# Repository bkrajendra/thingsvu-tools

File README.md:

<h1 align="center">thingsvu-tools</h1>

<p align="center">
  <b>AI-assisted design tools for embedded products — schematic, PCB, and enclosure — built on KiCad.</b>
</p>

<p align="center">

</p>

---

## What is thingsvu-tools?

thingsvu-tools lets an AI assistant work alongside you in KiCad. You describe the circuit you want; the assistant plans the change, shows you exactly what it will do, and — once you approve — builds it in your schematic. Every result is checked against KiCad itself before it is reported back to you.

It connects to any assistant that speaks the [Model Context Protocol](https://modelcontextprotocol.io) (MCP), such as Claude Desktop, Claude Code, or VS Code.

> [!NOTE]
> **Third-party tools.** Whole-board autorouting (`pcb_autoroute_plan`) is done by [Freerouting](https://github.com/freerouting/freerouting), a separate open-source project (GPL-3.0) by its own authors; thingsvu-tools is not affiliated with it. It is optional: it is only used after you set it up (see [Optional: the autorouter](#optional-the-autorouter)), runs on your machine with its network features turned off, and its results are checked by KiCad's own DRC before they are kept. Everything else, including explicit routing, pours, and placement, is done by thingsvu-tools and KiCad itself.

## Why it's different

- **You stay in control.** Changes are proposed as a plan first. Nothing touches your design until you confirm it, and a stale plan is never applied to a document that has changed.
- **Verified, not assumed.** After every change, the tools read the design back from KiCad — symbols, values, and net connections — and run ERC. A check that couldn't run is reported as such, never as a pass.
- **Readable schematics.** Generated schematics read like a person drew them: signal flows left to right, power and ground are symbols, parts are wired, not just labelled.
- **Describe intent, not coordinates.** Say "R1 pin 2 and R2 pin 1 share net MID"; the tools take care of placement, wiring, and labels on the proper grid.
- **Built on KiCad's official API.** First-class support for KiCad 11's schematic API, with a fallback that works on KiCad 10 through the schematic file. You always know which features your KiCad version supports.
- **Works live, headless, or on a file.** Co-edit in the open Schematic Editor with normal undo, generate and verify designs without a GUI, or edit a schematic file with no KiCad running at all.
- **Local and private.** Everything runs on your machine. No cloud service, no open network ports, and your design files stay where they are.
- **Fast and dependable.** Written in Rust as a small set of native binaries — no Python runtime to manage.

## Quick start (Windows)

You need **KiCad 11** (or the 10.99 nightly) for live editing, or **KiCad 10** for the file mode, and an AI assistant that supports MCP. No administrator rights are needed: everything is installed under your user profile.

### 1. Install

**Option A — download.** Get `thingsvu-tools-v<version>-windows-x64.zip` from the [latest release](https://github.com/bkrajendra/thingsvu-tools/releases/latest), extract it, and run `install.ps1` (right-click → **Run with PowerShell**).

**Option B — one line.** In PowerShell:

```powershell
irm https://raw.githubusercontent.com/bkrajendra/thingsvu-tools/main/scripts/install.ps1 | iex
```

This downloads the newest release, checks it against its published checksum, and installs it. Read the [script](scripts/install.ps1) first if you like; it is short.

The installer:

1. puts `kicad-ai-mcp.exe` in `%LOCALAPPDATA%\thingsvu\kicad-ai\bin`;
2. installs the **KiCad AI** plugin into your KiCad 11 plugin folder (`Documents\KiCad\<version>\plugins`) — KiCad 10 cannot run schematic plugins, so it is skipped there;
3. offers to add the server to **Claude Code** and **Claude Desktop** (it keeps a backup of any settings file it changes);
4. tells you what to do next.

Useful options: `-Yes` (answer yes to everything), `-NoPlugin`, `-SkipClients`, `-KicadVersion 11.0`, `-Version 0.1.0`.

### 2. Turn on KiCad's API (KiCad 11, live editing)

In KiCad: **Preferences → Plugins**, enable the **KiCad API**, then restart KiCad. If you only use the file mode, skip this.

### 3. Connect your assistant

The installer does this for Claude Code and Claude Desktop. For anything else, the server is a program that speaks MCP over stdio:

<details>
<summary><b>Claude Code</b></summary>

```powershell
claude mcp add --scope user kicad-ai -- "$env:LOCALAPPDATA\thingsvu\kicad-ai\bin\kicad-ai-mcp.exe"
```
</details>

<details>
<summary><b>Claude Desktop</b></summary>

Add to `%APPDATA%\Claude\claude_desktop_config.json`, then restart Claude Desktop:

```json
{
  "mcpServers": {
    "kicad-ai": {
      "command": "C:\\Users\\<you>\\AppData\\Local\\thingsvu\\kicad-ai\\bin\\kicad-ai-mcp.exe",
      "args": []
    }
  }
}
```
</details>

<details>
<summary><b>VS Code</b></summary>

Add to `.vscode/mcp.json` in your workspace:

```json
{
  "servers": {
    "kicad-ai": {
      "type": "stdio",
      "command": "C:/Users/<you>/AppData/Local/thingsvu/kicad-ai/bin/kicad-ai-mcp.exe"
    }
  }
}
```
</details>

Add `"--read-only"` to the arguments to let the assistant look but never change anything.

### Optional: the autorouter

To let the assistant route a whole board at once, set up [Freerouting](https://github.com/freerouting/freerouting) (a separate open-source program; see the note at the top). One step:

- **Installing now:** answer **y** when the installer asks *"Also set up whole-board autorouting?"*, or run it with `-WithFreerouting`.
- **Already installed:** run this one line in PowerShell:

  ```powershell
  & ([scriptblock]::Create((irm https://raw.githubusercontent.com/bkrajendra/thingsvu-tools/main/scripts/install.ps1))) -FreeroutingOnly
  ```

It uses a Freerouting already on your machine if it finds one that works (a running one, or Freerouting's own Windows install). Otherwise it downloads Freerouting from its official GitHub release: its native command-line build if that works, else its Java build together with a Java 25 runtime (Eclipse Temurin, from Adoptium) when you have none. Every download is checked against its published checksum, and whatever it settles on must route a small test board first. (Freerouting 2.5.0's native Windows build hangs on KiCad boards, so today it ends up with the Java build: about 120 MB with the runtime, a few minutes.) Everything goes under `%LOCALAPPDATA%\thingsvu\kicad-ai`, with a `config.json` there so the server finds it. Restart your assistant afterwards. The uninstaller removes it with everything else.

**Already have Freerouting?** Add `-FreeroutingPath <path to its .exe or .jar>` (and `-JavaPath <java.exe>` for a jar) to the line above; nothing is downloaded. You can also start the server with `--freerouting <path>` (and `--java <path>`), or set `THINGSVU_FREEROUTING`.

Without it, autorouting is simply unavailable and everything else works. Freerouting runs as a separate process for each plan, with its GUI, API server, and usage reporting turned off, so nothing leaves your machine.

### 4. Try it

Ask your assistant:

> Call `session_status` and tell me what KiCad installs and sessions you can see.

Then, with a schematic that is **not** open in KiCad (any KiCad version):

> Open `D:\projects\demo\demo.kicad_sch` with the file provider and build a 3.3 V regulator from 5 V: a fuse, a Schottky diode, an AMS1117-3.3 with decoupling capacitors, and a power LED. Show me the plan first.

Or live, with KiCad 11: open your project in the **Schematic Editor**, press the **KiCad AI: connect** toolbar button (a small dialog confirms), then:

> Open the schematic in my KiCad editor (gui provider) and add an NE555 astable blinker driving an LED.

The assistant plans, shows you the parts, positions, and nets, and waits for your OK. Applying a plan in the live editor is two undo steps (**Ctrl+Z** twice).

To clean up a schematic that already exists:

> Review the schematic, then plan a tidy and show me what would move before you change anything.

The tidy lays the circuit out again, keeping every part, value, and footprint and checking that every net is identical afterwards. It handles a single sheet of parts joined by wires, labels, and power symbols; buses, global labels, and hierarchical sheets are refused with a reason; no-connect flags stay on their pins (drawn again where a part moved), and text notes stay where they are.

To steer it, or to arrange a small circuit yourself:

> Keep J1 where it is and put C1 and C2 next to each other, then tidy.
>
> Move the regulator to the top right, group R1 and R2 below it, then reconnect everything.

To look at a board:

> Open D:/projects/mydesign/mydesign.kicad_pcb, review it, and tell me what the schematic has that the board lacks.

Boards are opened with `pcb_open` (headless needs KiCad 11 or the 10.99 nightly; the file provider also reads KiCad 10 boards for reading, DRC, and render). A board can be brought up to date from its schematic: the assistant shows what KiCad's own netlist import would add, and applies it only after you confirm. New footprints arrive stacked near the origin.

An assistant can then give the board an outline and move parts, through a live session (headless or the PCB editor; a file session only reads):

> Put a 50 x 40 mm outline with 2 mm rounded corners and an M3 hole in each corner around the parts, then turn U1 by 90 degrees and move C1 to the back.

Each change is shown as a plan first, applied as one step (one Ctrl+Z in the editor), and read back: the outline, and every moved footprint's place, turn, side, lock, pads, and nets, with KiCad's DRC run before and after. A change that fails those checks, or makes DRC worse, is undone automatically and the board is read again to confirm it is as it was. Locked footprints stay where they are unless you say otherwise.

Once the board has an outline, the assistant can place every part:

> Place the parts on the board. Keep J1 on the left edge and put the LED near the connector.

The main IC goes in the middle, connectors on an edge, decoupling capacitors beside the pins they serve, and everything else near what it connects to, with no overlaps; parts you drew a box around on the schematic stay together. The plan shows the measured result before and after (wire length, overlaps, distances) so you can judge it, and individual parts can be adjusted afterwards with a move.

Tracks are planned the same way:

> Route VBUS from J1 to the fuse, then run +3V3 from U1 pin 2 to C3 on the top layer, dropping to the bottom layer through a via at 112, 90.

Between two pads the assistant finds a simple path (straight, 45°, or an L) on a layer both pads are on; with more points it follows them, placing a via wherever the layer changes. Widths, clearances, and via sizes come from your board's net classes. Every track and via is checked against other nets' copper and the board edge before anything changes, and DRC runs before and after applying, so you see the unrouted count drop and any new error. Copper pours too:

> Pour ground on both layers, with thermal reliefs, and tell me which connections are still missing.

The pour covers the board (or an area you give) at your net class's clearance; the plan lists the pads it should connect, applying refills it and runs DRC before and after.

With Freerouting set up ([one step](#optional-the-autorouter)), the whole board can be routed at once:

> Autoroute the board and tell me if anything is left.

The plan runs Freerouting on a snapshot of the board and shows its result (unrouted connections, tracks per net, the unlocked tracks it would replace) before anything changes; applying imports it into KiCad and checks that no part moved and DRC is no worse. Lock the tracks you want to keep.

When the board is done, the assistant makes the files to order it:

> Check the board and make a JLCPCB package.

Before anything is written, the board is checked: the outline is closed, DRC has no errors and nothing is unrouted, every footprint has a BOM line, and the silkscreen stays on the board. If a check fails, you see why and nothing is written, unless you say to go ahead anyway; that decision is recorded in a checks report beside the files. `pcb_fab_package` then writes, into a `fab` folder next to the board, the Gerbers and drill files as one zip (what you upload for the bare board), the BOM and placement (CPL) files in JLCPCB's columns, and one `<board>-fab.zip` with all of it. `pcb_export` writes the pieces separately (Gerbers, drill, positions, STEP, PDF or SVG plots). Every file is read back before it is kept: the copper layer count, the outline, every drill hole against the board's holes, the placement rows against the parts, and, with KiCad 11, every Gerber through the same reader KiCad's Gerber viewer uses. Nothing is uploaded.

For an enclosure, ask for the board's mechanical summary:

> What are the board's size and mounting holes, which edge does the USB connector face, and how tall is the tallest part?

`pcb_mechanical_info` returns the outline and thickness, mounting holes, keep-out areas, connectors and the edge each one faces, and each part's height. A height comes from the part's `Height` field, or else from a typical height for its package, marked as an estimate.

To get a schematic ready to order parts:

> Review the BOM for a JLCPCB order. Look up the parts you can, fill in the part numbers, assign the missing footprints, and export the BOM.

The server looks nothing up and makes no network calls. `bom_review` lists what is missing, with a search hint for each line; the assistant finds the parts with whatever parts-lookup tool it has (a JLCPCB, Mouser, or DigiKey connector, for example) and records the answers with `sch_set_fields_plan` (fields `MPN`, `Manufacturer`, `LCSC`). With no such tool the fields stay empty and the review keeps saying so.

After a tidy or a reconnect, KiCad decides where the text of each part lands, and it can run into a wire or another part's text. Ask for it to be cleaned up:

> Check the schematic for text that overlaps, and move it.

Labels, notes, and drawings can be edited too:

> Put a box around U1, C1 and C2 titled "Regulator", and add a label OUT on R3 pin 2.

Moving, turning, or deleting a part leaves its wires behind, so the circuit is broken until you ask for **reconnect**, which draws every connection again around the parts where they now are (and checks every net against KiCad). Good for the start of a design and for small circuits; for a whole sheet use the tidy.

## Three ways to work

| Provider | KiCad | What it does | Choose it when |
|---|---|---|---|
| `gui` | 11 | Edits the schematic open in your editor, live, with undo | You want to co-edit and watch it happen |
| `headless` | 11 | Starts a private KiCad in the background and works on a file | You want to generate or check designs without a GUI |
| `file` | 10 or 11 | Edits the `.kicad_sch` file itself; every change is verified with `kicad-cli` in a copy before it replaces the file | You use KiCad 10, or want no KiCad running. The file must not be open in an editor |

What each can do in detail: [capability matrix](docs/capability-matrix.md).

## Tools

| Tool | What it does |
|---|---|
| `session_status` | KiCad installs found, open sessions, what each can do, and whether the autorouter is set up |
| `session_open` / `session_close` / `session_reload` | Open a schematic (or create one), close it again, or read it from its file again after the file changed or to drop changes (refuses with unsaved changes unless told, and lists what would be lost). `read_only: true` opens a file an editor has locked, for reading only. `session_status` says whether the file changed on disk since the session read it |
| `session_list_documents` | Documents open in the session's KiCad |
| `sch_list_symbols` / `sch_get_symbol_pins` | Read parts and their pins, positions, and types |
| `sch_get_netlist` | Connectivity as KiCad's netlister sees it |
| `sch_plan_changes` | Turn a circuit (parts and nets) into an exact, reviewable plan. Changes nothing |
| `sch_apply_plan` | Apply a plan you confirmed (new circuit or tidy), verify it against KiCad, and report any difference |
| `sch_review` | Look at an existing schematic: overlapping parts, wires through parts, and whether it can be tidied. Read-only |
| `sch_tidy_plan` | Plan a cleaner layout for an existing schematic: parts re-laid out, old wires and labels replaced, nets kept identical. Optional hints: `keep`, `place`, `near`. Changes nothing until applied |
| `sch_describe_layout` | Where every part and pin is (mm), its rotation and body, and the net of each pin. Read-only |
| `sch_arrange_plan` | Plan moving, turning, mirroring, or deleting named parts. Their wires stay and break until reconnected |
| `sch_pin_net_plan` | Move one pin to another net, or swap the nets of two pins, changing only those pins' wire, label, or power symbol (a short stub that names the new net); every net is read back from KiCad |
| `sch_reconnect_plan` | Plan drawing all connections again with the parts where they are, for the circuit as it was before the moves |
| `sch_declutter_plan` | Find text (part references and values, labels) that runs into other text, a wire, or a part, and plan moving it to a free place; `PWR_FLAG` text that has no room is hidden. Only text changes |
| `sch_label_plan` | Add, rename, turn, or delete net labels. Refuses a label that would give a net a second name or join two nets by accident |
| `sch_draw_plan` | Draw rectangles, circles, lines, text notes, and a titled box around named parts (for example "Power supply") |
| `sch_edit_items_plan` | Delete wires, labels, junctions, notes, and drawings by id, or move labels, notes, and drawings |
| `bom_get` | The bill of materials as KiCad groups it, with every custom field. Read-only |
| `bom_review` | What an order lacks: footprints, part numbers, supplier numbers, inconsistent values; plus a list of lookups to do. No network |
| `sch_set_fields_plan` | Set fields on many parts at once: part numbers, manufacturer, datasheet, DNP, exclude from BOM (custom fields are added hidden) |
| `sym_search` / `sym_get` | Search the symbol libraries by name, keyword, or description (default footprint and filters, pins, units) and read one symbol's pins without placing it |
| `fp_search` / `fp_get` | Search the footprint libraries and read a footprint's pads and courtyard |
| `sch_footprint_plan` | Check every footprint (missing, not in the libraries, no pad for a pin, wrong package) and assign footprints |
| `bom_export` | Write the BOM as CSV into the project folder (generic or JLCPCB columns) |
| `pcb_open` / `pcb_close` / `pcb_save` / `pcb_reload` | Open a board (headless, file, or the PCB editor; `read_only: true` for a file session on a board an editor has open), close it, save it, or read it from its file again (`pcb_info` says when the file changed on disk or the board has unsaved changes; a reload with unsaved changes lists what it would lose and needs `discard_unsaved`) |
| `pcb_info` / `pcb_list_footprints` / `pcb_get_footprint` / `pcb_list_nets` / `pcb_list_tracks` | Read the board: counts, outline, footprints with pads and courtyards, nets, tracks, vias, zones. `detail: full` (with `references` to narrow it) adds each pad's shape, size, drill, and turn, the courtyard outline, and the footprint's text and fields with layer, size, place, and visibility |
| `pcb_list_drawings` | The drawings and text on the board itself (not in footprints): lines, rectangles, circles, arcs, polygons, and text, with layer, points, line width, fill, and lock; narrowed by layers and kinds |
| `pcb_run_drc` / `pcb_render` | Design rules check (zones refilled first; counts by type, with `summary_only`, `severity`, `types`, and `limit` to keep a big board readable; unrouted connections) and a 3D picture of the board |
| `pcb_review` | What stands out: overlaps, parts outside the outline, no outline, schematic and board that disagree, far connectors and decoupling capacitors, DRC |
| `pcb_update_from_schematic_plan` / `pcb_apply_plan` | Update the board from its schematic: a dry run first, then apply after you confirm; every footprint and pad net is checked afterwards |
| `pcb_outline_plan` | A board outline (rectangle, rounded corners) of a given size or fitted around the parts, with mounting holes in the corners or at given places; applied with `pcb_apply_plan` |
| `pcb_footprint_attrs_plan` | Set do-not-populate, BOM, position-file, and board-only attributes on named footprints, or on every mounting hole (repairs holes from boards made with v0.7.0); applied with `pcb_apply_plan`, read back |
| `pcb_move_plan` | Move, turn, flip, and lock named footprints (places on a grid, exact offsets); shows overlaps before and after; applied with `pcb_apply_plan`, every pad read back |
| `pcb_route_plan` | Tracks and vias for named nets, pad to pad or through given points, at the net class width (`locked: true` locks what a route makes); checked against other nets' copper and the edge; DRC before and after applying |
| `pcb_rules` / `pcb_rules_plan` | Read the design rules (net classes and the nets in each, minimums, mask and paste margins, stackup) and change them: create or change net classes (track width, clearance, via size and drill, differential pair), assign nets by name or pattern, set the board minimums. Applied with `pcb_apply_plan` and read back; in a live session through the API, with no editor through the project file (checked by `kicad-cli`, backup kept) |
| `checkpoint_create` / `checkpoint_list` / `checkpoint_diff` / `checkpoint_restore` | Keep copies of the project's board, schematic, and project file in `.thingsvu/checkpoints/` (a live session's unsaved changes included), list them, compare one with another or with the project now by meaning (parts, nets, tracks, zones, rules), and put one back. A restore refuses over unsaved changes, takes a checkpoint of the present first, and reloads the sessions. `pcb_apply_plan` takes `checkpoint: label` to keep one first |
| `pcb_track_edit_plan` | Edit copper already on the board: delete (rip up) tracks and vias by net, layer, area, or id, give tracks a new width, lock and unlock, and clean up dangling vias, zero-length and duplicate tracks. Locked items are skipped unless named; the plan lists every item and a count per net; applied with `pcb_apply_plan` (one change, read back, DRC before and after) |
| `pcb_zone_plan` | Copper pours (ground first) over the board or an area, with clearance, minimum width, and thermal reliefs; refilled after applying, DRC before and after |
| `pcb_autoroute_plan` | Route the board with Freerouting (optional, when configured), all nets or only some (`nets`, `exclude_nets`), keeping what is drawn (`keep_existing`, default) or ripping up the unlocked tracks of the nets it routes (`keep_existing: false`); net classes give nets their widths; the time limit ends the router and everything it started: the router's result first (wires narrower than the board's minimum are widened), then KiCad's import, dangling vias removed, checked with DRC before and after |
| `pcb_export` | Gerbers, drill, positions, STEP, PDF/SVG plots, and the mechanical model, into the project, after the pre-export checks; every file read back |
| `pcb_fab_package` | The files a board house needs (Gerber zip, BOM, CPL; JLCPCB or generic columns) and one zip with all of them and the checks report |
| `pcb_mechanical_info` | Outline, thickness, mounting holes, keep-outs, connectors and the edge each faces, and part heights, for enclosure design. Read-only |
| `pcb_place_plan` | Place the footprints inside the outline (main IC central, connectors on edges, decoupling beside its pins, no overlaps), with hints keep, place, near, edge, groups, side, only; measured before and after; applied with `pcb_apply_plan` |
| `sch_set_field` | Change one part's value or footprint |
| `sch_save` | Save the schematic |
| `sch_run_erc` | Electrical rules check |
| `sch_export_netlist` | Write a KiCad netlist |
| `sch_render` | A PNG of the schematic, so the layout can be checked visually |
| `sch_create_demo_circuit` | A two-resistor demo for a quick end-to-end check |

## Troubleshooting

| Problem | What to do |
|---|---|
| No **KiCad AI: connect** button | Restart KiCad after installing. The plugin must be in `Documents\KiCad\<version>\plugins\com.thingsvu.kicad-ai` (your Documents folder may be redirected, e.g. to OneDrive; the installer handles that). It needs KiCad 11 or the 10.99 nightly, and the button appears in the Schematic Editor |
| `session_status` shows no editors | Enable the KiCad API in Preferences → Plugins, restart KiCad, then press the button again |
| `DOCUMENT_OPEN_ELSEWHERE` | The file is open in a KiCad editor. Use the `gui` provider for that editor, or close it before using `file` or `headless` |
| `STALE_PLAN` | The schematic changed after the plan was made. Ask for a new plan |
| `FEATURE_UNAVAILABLE` for rendering | KiCad 10's `kicad-cli` cannot export PNG. Install KiCad 11 (or the 10.99 nightly) next to it |
| "format version … is older" | Open and save the file once in KiCad 10, or run `kicad-cli sch upgrade <file>`, then try again |
| A symbol is not found | Symbols come from the schematic itself, the project's `sym-lib-table`, and KiCad's standard libraries. Libraries only in your global library table are not read yet |
| Windows SmartScreen warning | The binaries are not code-signed yet. Compare the file's SHA-256 with `SHA256SUMS.txt` on the release page |
| Something else | Logs are in `%LOCALAPPDATA%\thingsvu\kicad-ai\logs` (the last 7 days). Run `kicad-ai-mcp --help` for options |

## Updating and removing

- **Update:** run the installer again (a newer release replaces the old files). Close your assistant first if it holds the server open.
- **Remove:** run `%LOCALAPPDATA%\thingsvu\kicad-ai\uninstall.ps1`. It removes the server, the plugin, registrations, logs, and the assistant entries the installer added, and nothing else. Your schematics and KiCad's own settings are never touched.

## What's included

| Component | What it does |
|---|---|
| **kicad-ai-mcp** | The MCP server your AI assistant talks to |
| **kicad-ai-plugin** | A KiCad plugin that makes your open editor available to the assistant |
| **kicad-domain** | The shared circuit model: plans, validation, layout, and readability checks |
| **kicad-session**, **kicad-ipc**, **kicad-sexpr**, **kicad-cli-runner** | Sessions over KiCad's API or a schematic file; the API client; KiCad file reading and writing; `kicad-cli` jobs |
| **mech-model** | A neutral description of the board for mechanical design (no KiCad types), the start of the enclosure tools |

```mermaid
flowchart LR
    A["AI assistant"] <-->|MCP| S["kicad-ai-mcp"]
    S -->|"KiCad 11 API"| G["KiCad 11 editor<br/>(live, with undo)"]
    S -->|"KiCad 11 API"| H["private headless KiCad"]
    S -->|"verified file edits"| F[("schematic file<br/>KiCad 10 or 11")]
    P["kicad-ai-plugin<br/>toolbar button"] -.->|"registers the editor"| S
    S -->|"ERC, DRC, netlist, render,<br/>Gerbers, drill, STEP"| C["kicad-cli"]
```

More detail: [architecture](docs/architecture.md).

## Build from source

You need [Rust](https://rustup.rs) (stable) and [`protoc`](https://github.com/protocolbuffers/protobuf/releases) on your `PATH`.

```powershell
cargo build --release -p kicad-ai-mcp -p kicad-ai-plugin
cargo test --workspace                         # no KiCad needed
$env:KICAD_LIVE = '1'; cargo test --workspace -- --test-threads=1   # against your KiCad installs
.\scripts\package.ps1                           # release zip, PCM zip, checksums in .\dist
.\scripts\install-plugin.ps1                    # developers: just the plugin, from your build
```

How releases are made: [releasing](docs/releasing.md).

## Roadmap

- **Now:** schematic inspection and editing, readable generated schematics (signal flow left to right, power symbols, wires), reviewing and tidying existing schematics, ERC, netlist export, verified demo circuits, KiCad 10 through the schematic file, and a one-step installer
- **Now (also):** parts, footprints, and BOM review and export
- **Now (also):** reading, DRC, rendering, and reviewing boards, and updating a board from its schematic
- **Now (also):** board outline, placement, routing, pours, and autorouting (optional, with Freerouting)
- **Now (also):** manufacturing outputs (Gerbers, drill, BOM and placement files, STEP) with checks before export, and a mechanical summary of the board
- **In progress (Phase 14, not released yet):** done so far: the planned part's custom fields are written, DRC results are summaries with only the new violations after a change, zones are refilled before DRC, autorouting keeps the minimum track width and removes dangling vias, circuit plans and the tidy take 150 parts, and the tidy keeps no-connect flags. Next: track editing, design rules, session reload, checkpoints.
- **Next (Phase 13b fixes, then Phases 14 to 16, see [docs/workflow-gaps-plan.md](docs/workflow-gaps-plan.md)):** text that follows turned parts, a repair for older mounting holes, track editing and rip-up, net classes and design rules, reloading and checkpoints, schematic no-connects and pin swaps, footprint and silkscreen edits, stitching and connectivity checks
- **Also open:** hierarchical schematics
- **Later:** 3D enclosure design driven from your PCB, so the whole embedded product comes together in one workflow

## Project status

thingsvu-tools is in early development and is not ready for production designs yet. The architecture and plan are in [`docs/`](docs/README.md).

AI-generated designs do not replace qualified engineering review. Always review and verify a design before manufacturing it.

## Supported KiCad versions

| KiCad | Support |
|---|---|
| 11 (currently nightly 10.99) | First-class: full schematic editing, live and headless |
| 10.0.x | Fallback through the schematic file: inspection, ERC, netlist, and editing of schematics no editor has open (each change is checked with `kicad-cli` before it replaces the file) |

## Sponsor

If thingsvu-tools is useful to you, please consider [sponsoring its development](https://github.com/sponsors/bkrajendra). Sponsorship helps keep the project independent and moving forward.

## License

thingsvu-tools is free software, licensed under the [GNU General Public License v3.0 or later](LICENSE). thingsvu-tools is an independent project and is not affiliated with or endorsed by the KiCad project.

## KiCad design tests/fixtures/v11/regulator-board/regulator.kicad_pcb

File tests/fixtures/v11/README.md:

# KiCad 11 fixtures

Files written by KiCad itself (10.99 nightly `10.99.0-5896-gd033635628`, schematic format `20261015`). Do not edit them by hand; regenerate them with KiCad instead. KiCad 10 cannot open these files.

| Fixture | Source |
|---|---|
| `empty-schematic/` | New project created in the 10.99 GUI |
| `two-resistor-series-chain/` | `empty-schematic` after the Rust probe `demo` scenario on the headless server. Values were set with `UpdateItems` without the embedded library definition and with field mask `value_field`. One library symbol (`Device:R`); R1 and R2 are `10k` |

Expected connectivity for `two-resistor-series-chain` (from `kicad-cli sch export netlist`, matching `docs/examples/two-resistor-series-chain.json`):

| Net | Nodes |
|---|---|
| `/INPUT` | R1.1 |
| `/MID` | R1.2, R2.1 |
| `/OUTPUT` | R2.2 |

ERC (`kicad-cli sch erc --severity-all`): 2 warnings, `isolated_pin_label` on INPUT and OUTPUT. This is expected, because those nets have one pin each.

History: earlier versions of this fixture were wrong. The first headless one duplicated the library symbol (`R_1`) because whole symbols were sent back in one batch. A GUI-saved one kept Value `R` although `UpdateItems` replied `10k`. Replaced on 24 Oct 2026; see `docs/tasks.md` (tasks 1.4 and 2.6).

| `regulator-with-notes/` | The 3.3 V regulator from `docs/examples/regulator-3v3.json`, built with these tools in the 10.99 GUI and then edited by an AI assistant (a title and a note added, labels and flags moved). A realistic starting point for the tidy tests: 13 parts, 11 power symbols, wires, junctions, two text notes. Do not edit by hand |

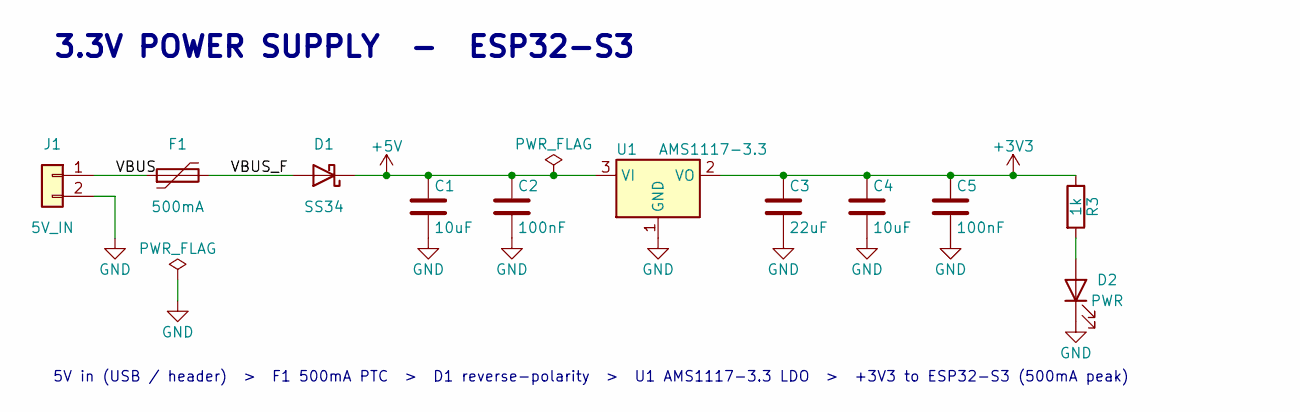
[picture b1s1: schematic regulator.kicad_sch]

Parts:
C1, C4: 10uF; C_0805_2012Metric
C2, C5: 100nF; C_0603_1608Metric
C3: 22uF; C_1206_3216Metric
D1: SS34; D_SMA
D2: PWR; LED_0603_1608Metric
F1: 500mA; Fuse_1206_3216Metric
J1: 5V_IN; PinHeader_1x02_P2.54mm_Vertical
R3: 1k; R_0603_1608Metric
U1: AMS1117-3.3; SOT-223-3_TabPin2

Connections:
+3V3: C3.1, C4.1, C5.1, R3.1, U1.2 (VO)
+5V: C1.1, C2.1, D1.1 (K), U1.3 (VI)
/VBUS: F1.1, J1.1
/VBUS_F: D1.2 (A), F1.2
GND: C1.2, C2.2, C3.2, C4.2, C5.2, D2.1 (K), J1.2, U1.1 (GND)
unnamed: D2.2 (A), R3.2

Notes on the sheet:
3.3V POWER SUPPLY - ESP32-S3
5V in (USB / header) > F1 500mA PTC > D1 reverse-polarity > U1 AMS1117-3.3 LDO > +3V3 to ESP32-S3 (500mA peak)

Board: 2 copper layers, 11 parts (0 on the bottom side), 6 nets, no tracks yet.

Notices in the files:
README.md:
License: GPL-3.0-or-later
